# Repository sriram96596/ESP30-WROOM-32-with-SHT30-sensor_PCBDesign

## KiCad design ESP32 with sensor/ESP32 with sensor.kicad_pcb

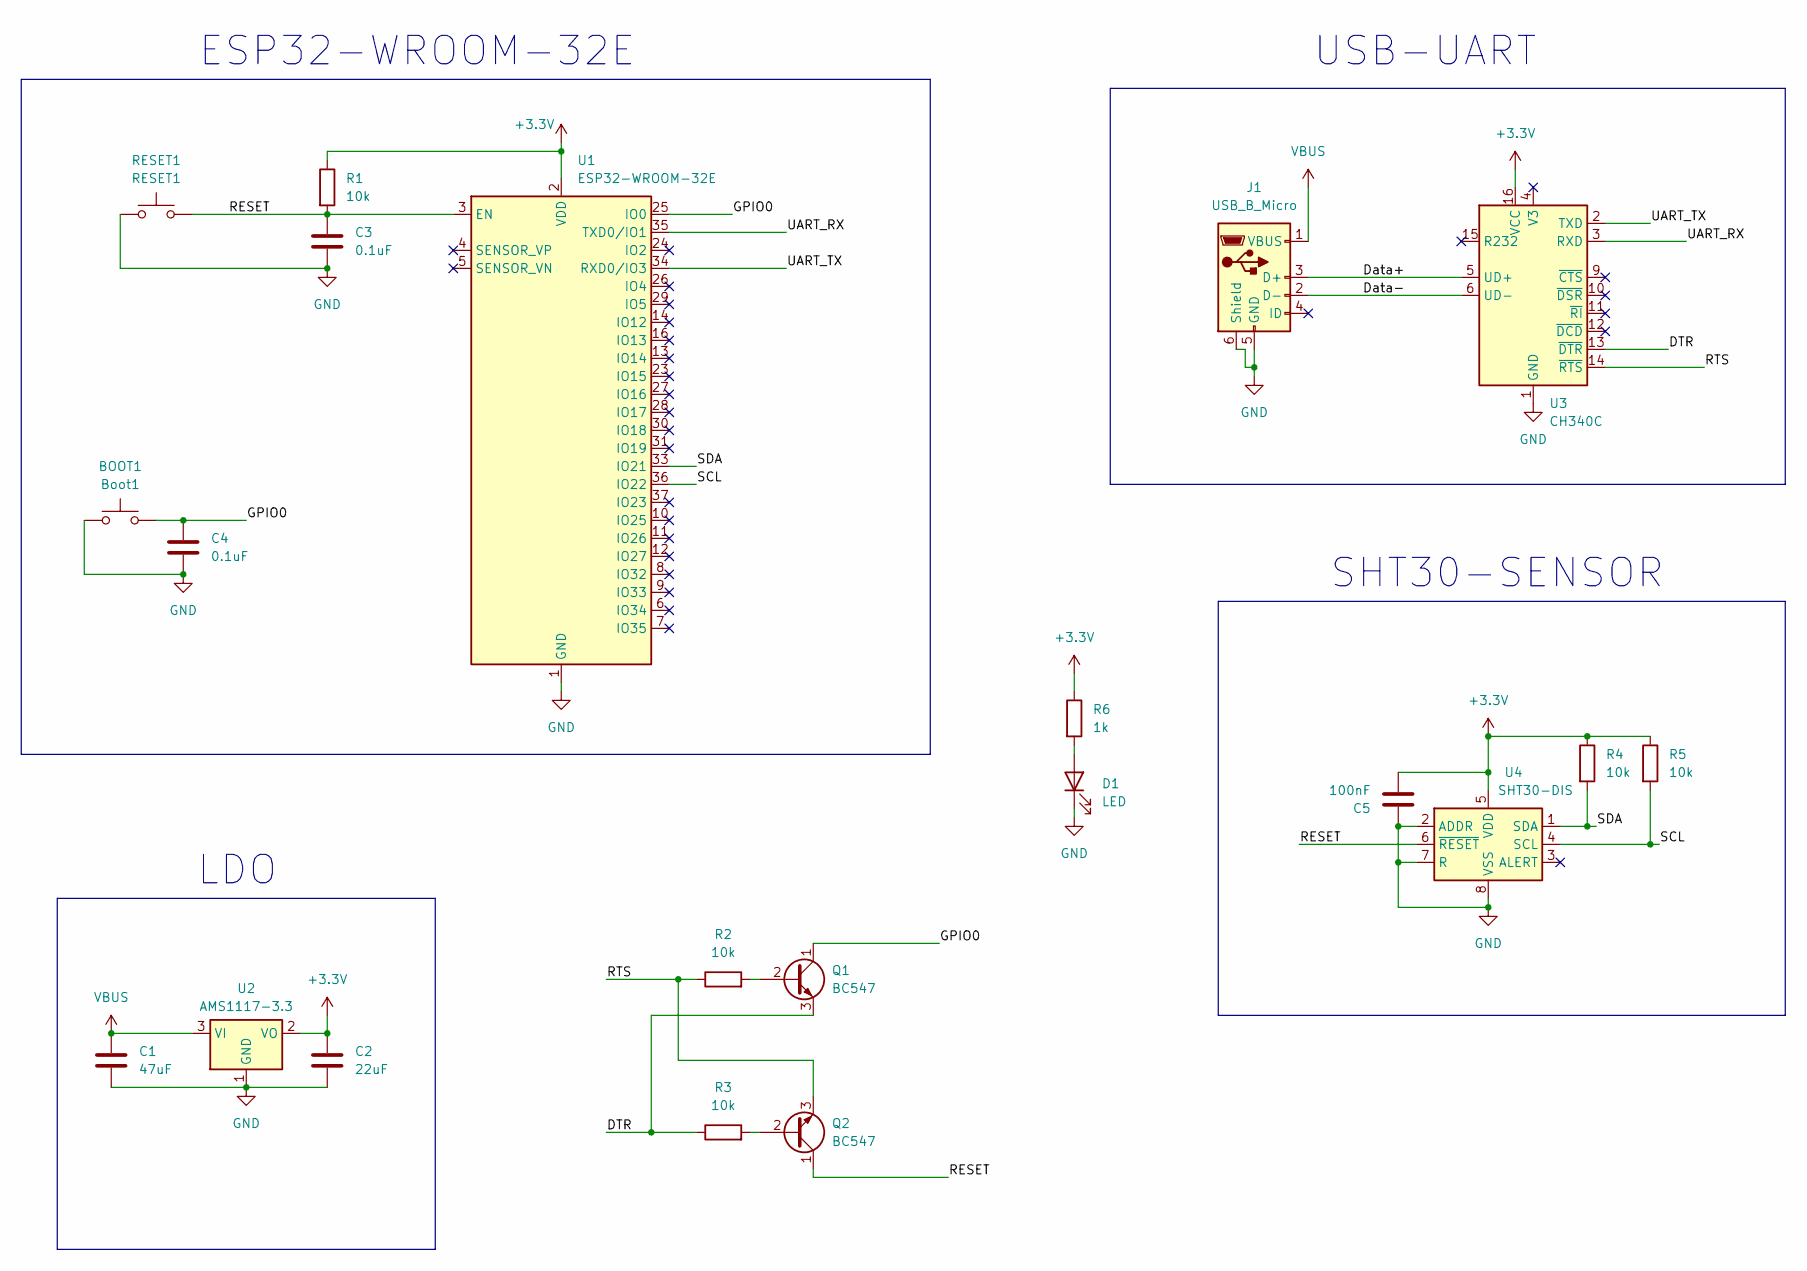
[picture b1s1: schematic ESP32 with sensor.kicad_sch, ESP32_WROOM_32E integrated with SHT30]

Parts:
BOOT1: Boot1; SW_Push_1P1T_NO_CK_KSC6xxJ
C1: 47uF; C_Elec_6.3x5.4
C2: 22uF; C_Elec_5x5.4
C3, C4: 0.1uF; C_0603_1608Metric_Pad1.08x0.95mm_HandSolder
C5: 100nF; C_1206_3216Metric_Pad1.33x1.80mm_HandSolder
D1: LED; LED_1210_3225Metric_Pad1.42x2.65mm_HandSolder
J1: USB_B_Micro; USB_Micro-B_Molex_47346-0001
Q1, Q2: BC547; SOT-23-3
R1, R2, R3, R4, R5: 10k; R_0603_1608Metric_Pad0.98x0.95mm_HandSolder
R6: 1k; R_1206_3216Metric_Pad1.30x1.75mm_HandSolder
RESET1: RESET1; SW_Push_1P1T_NO_CK_KSC6xxJ
U1: ESP32-WROOM-32E; ESP32-WROOM-32D
U2: AMS1117-3.3; SOT-223-3_TabPin2
U3: CH340C; SOIC-16_3.9x9.9mm_P1.27mm
U4: SHT30-DIS; Sensirion_DFN-8-1EP_2.5x2.5mm_P0.5mm_EP1.1x1.7mm

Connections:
+3.3V: C2.1, C5.2, R1.1, R4.1, R5.1, R6.1, U1.2 (VDD), U2.2 (VO), U3.16 (VCC), U4.5 (VDD)
/DTR: Q1.3 (E), R3.1, U3.13 (~DTR)
/GPIO0: BOOT1.2, C4.1, Q1.1 (C), U1.25 (IO0)
/RESET: C3.1, Q2.1 (C), R1.2, RESET1.2, U1.3 (EN), U4.6 (~RESET)
/RTS: Q2.3 (E), R2.1, U3.14 (~RTS)
/SCL: R5.2, U1.36 (IO22), U4.4 (SCL)
/SDA: R4.2, U1.33 (IO21), U4.1 (SDA)
/UART_RX: U1.35 (TXD0/IO1), U3.3 (RXD)
/UART_TX: U1.34 (RXD0/IO3), U3.2 (TXD)
GND: BOOT1.1, C1.2, C2.2, C3.2, C4.2, C5.1, D1.1 (K), J1.5 (GND), J1.6 (Shield), RESET1.1, U1.1 (GND), U1.15 (GND), U1.38 (GND), U1.39 (GND), U2.1 (GND), U3.1 (GND), U4.2 (ADDR), U4.7 (R), U4.8 (VSS), U4.9 (VSS)
unnamed: D1.2 (A), R6.2
unnamed: J1.3 (D+), U3.5 (UD+)
unnamed: J1.2 (D-), U3.6 (UD-)
unnamed: Q1.2 (B), R2.2
unnamed: Q2.2 (B), R3.2
VBUS: C1.1, J1.1 (VBUS), U2.3 (VI)

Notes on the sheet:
ESP32-WROOM-32E
LDO
SHT30-SENSOR
USB-UART

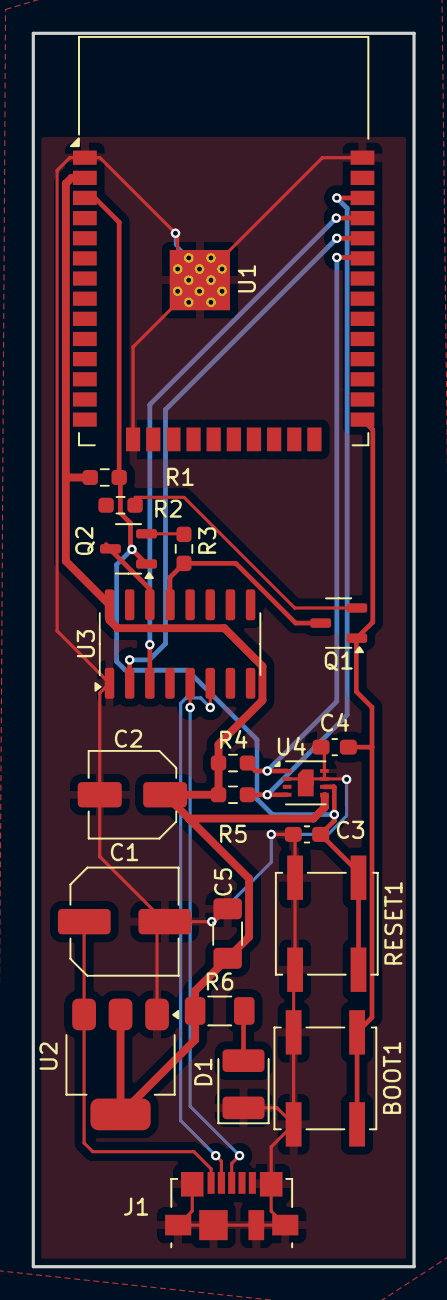
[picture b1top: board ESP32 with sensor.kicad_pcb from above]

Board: 2 copper layers, 24.0 x 77.8 mm, 21 parts (0 on the bottom side), 16 nets.

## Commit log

2024-11-01 ESP30-WROOM-32-with-SHT30-sensor_PCBDesign
